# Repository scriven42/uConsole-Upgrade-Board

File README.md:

# uConsole-Upgrade-Board

A board to upgrade the uConsole, expanding the GPIO and unused USB with i2c headers and a USB2 hub.

It connects to the 40-pin, 0.5mm pitch GPIO FFC/FPC connector, as well as being soldered to the unallocated USB4 pads. It splits out 3.3V I2C, providing a Qwiic connector (JST-SH) and soldering headers, and also provides a GL850-based USB2 Hub, the 4 ports accessible by soldering headers.

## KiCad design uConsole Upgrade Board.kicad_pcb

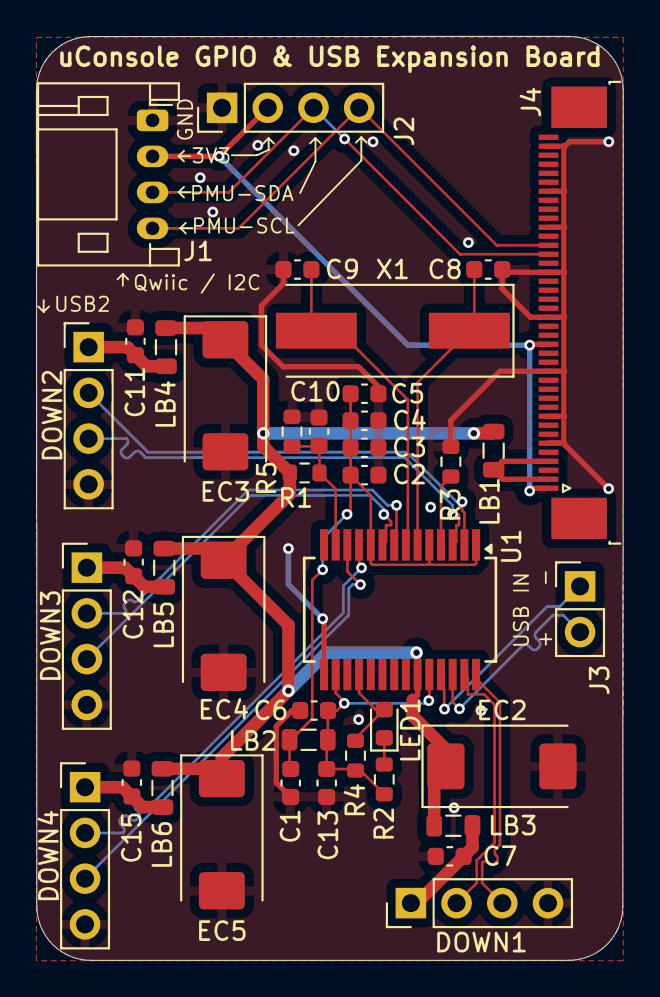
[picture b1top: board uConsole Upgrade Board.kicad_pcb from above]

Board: 4 copper layers, 32.6 x 51.3 mm, 40 parts (0 on the bottom side), 28 nets.

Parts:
C1: 1uF; C_0603_1608Metric
C2, C3, C4, C5, C6, C7, C10, C11, C12, C15: 0.1uF; C_0603_1608Metric
C8, C9: 20P; C_0603_1608Metric
C13: 10uF; C_0603_1608Metric
DOWN1, DOWN2, DOWN3, DOWN4: USBA-A; PinHeader_1x04_P2.54mm_Vertical
EC2, EC3, EC4, EC5: 100uF; CP_EIA-7343-31_Kemet-D
J1: Conn_01x04_Pin; JST_PH_S4B-PH-K_1x04_P2.00mm_Horizontal
J2: Conn_01x04_Pin; PinHeader_1x04_P2.54mm_Vertical
J3: Conn_01x02_Pin; PinHeader_1x02_P2.54mm_Vertical
J4: Conn_01x40; TE_4-1734839-0_1x40-1MP_P0.5mm_Horizontal
LB1, LB2, LB3, LB4, LB5, LB6: FB; L_0805_2012Metric
LED1: PWR_LED; LED_0603_1608Metric
R1: 10K; R_0603_1608Metric
R2: 470R; R_0603_1608Metric
R3: 680R 1%; R_0603_1608Metric
R4: 100K; R_0603_1608Metric
R5: 47K; R_0603_1608Metric
U1: GL850AUSB; SSOP-28_5.3x10.2mm_P0.65mm
X1: 12MHz; Crystal_SMD_HC49-SD

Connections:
+3.3V: J1.2, J2.2, J4.1, J4.17
+5V: J4.2, J4.4, LB1.1
/GL850G-USB2.0-HUB/PGANG: LED1.2, R4.1, U1.18 (PGANG)
/GL850G-USB2.0-HUB/RESET#: C10.2, R1.1, R5.2, U1.13 (RESET#)
/GL850G-USB2.0-HUB/RREF: R3.2, U1.4 (RREF)
/GL850G-USB2.0-HUB/USB_D1+: DOWN1.3 (D+), U1.28 (DP1)
/GL850G-USB2.0-HUB/USB_D1-: DOWN1.2 (D-), U1.27 (DM1)
/GL850G-USB2.0-HUB/USB_D2+: DOWN2.3 (D+), U1.3 (DP2)
/GL850G-USB2.0-HUB/USB_D2-: DOWN2.2 (D-), U1.2 (DM2)
/GL850G-USB2.0-HUB/USB_D3+: DOWN3.3 (D+), U1.9 (DP3)
/GL850G-USB2.0-HUB/USB_D3-: DOWN3.2 (D-), U1.8 (DM3)
/GL850G-USB2.0-HUB/USB_D4+: DOWN4.3 (D+), U1.12 (DP4)
/GL850G-USB2.0-HUB/USB_D4-: DOWN4.2 (D-), U1.11 (DM4)
/GL850G-USB2.0-HUB/X1: C8.2, U1.6 (XTAL1), X1.1
/GL850G-USB2.0-HUB/X2: C9.2, U1.7 (XTAL2), X1.2
/GPIO0: J1.3, J2.3, J4.27
/GPIO1: J1.4, J2.4, J4.28
/USB_D_IN+: J3.2, U1.26 (DP0)
/USB_D_IN-: J3.1, U1.25 (DM0)
AVDD: C1.2, C2.2, C3.2, C4.2, C5.2, LB2.1, U1.1 (AVDD1), U1.5 (AVDD2), U1.10 (AVDD3)
DVDD: C6.2, C13.2, LB2.2, R2.2, R4.2, U1.16 (DVDD), U1.24 (V33)
GND: C1.1, C2.1, C3.1, C4.1, C5.1, C6.1, C7.1, C8.1, C9.1, C10.1, C11.1, C12.1, C13.1, C15.1, DOWN1.4 (GND), DOWN2.4 (GND), DOWN3.4 (GND), DOWN4.4 (GND), EC2.2, EC3.2, EC4.2, EC5.2, J1.1, J2.1, J4.6, J4.9, J4.14, J4.20, J4.25, J4.30, J4.34, J4.39, R3.1, R5.1, U1.15 (GND)
unnamed: C7.2, DOWN1.1 (VCC), LB3.1
unnamed: C11.2, DOWN2.1 (VCC), LB4.1
unnamed: C12.2, DOWN3.1 (VCC), LB5.1
unnamed: C15.2, DOWN4.1 (VCC), LB6.1
unnamed: LED1.1, R2.1
VCC: EC2.1, EC3.1, EC4.1, EC5.1, LB1.2, LB3.2, LB4.2, LB5.2, LB6.2, R1.2, U1.23 (V5)

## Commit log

2024-10-10 Created.
2024-10-10 added README.md
2024-10-10 Initial Readme edits
2024-10-10 Further Readme editing, added more detail.
